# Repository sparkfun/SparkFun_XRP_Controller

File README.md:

SparkFun XRP Controller
========================================

<table>
    <tr>
        <td></td>
        <td></td>
    </tr>
    <tr>
        <th style="text-align: center;"><a href="https://www.sparkfun.com/sparkfun-experiential-robotics-platform-xrp-controller.html"><i>SparkFun XRP Controller</i></a></th>
        <th style="text-align: center;"><a href="https://www.sparkfun.com/sparkfun-experiential-robotics-platform-xrp-controller-beta.html"><i>SparkFun XRP Controller - Beta</i></a></th>
    </tr>
</table>

The Experiential Robotics Platform (XRP) Controller and Experiential Robotics Platform (XRP) Controller - Beta operate as the "brains" of the Experiential Robotics Platform Kits. These boards provide the programming and operation interface to connect and control the motors, sensors and other peripherals included in the XRP Kits. The controller boards primary microcontrollers are a Pico W (XRP-Beta) and RP2350 (XRP) and also include motor drivers, 6 DoF IMU, motor and sensor connectors along with other user interfaces.

Repository Contents
-------------------

* **/Documents** - Data sheets, additional product information
* **/Hardware** - Eagle design files (.brd, .sch)
* **/Production** - Production panel files (.brd)
* **/docs** - GitHub Pages documentation files (.md, images)

Documentation
--------------

* **[Hardware Overview](https://docs.sparkfun.com/SparkFun_XRP_Controller/introduction/)** - Basic hardware overview for the XRP Controller - Beta and XRP Controller.
* **[Experiential Robotics Platform Org](https://experientialrobotics.org/)** - Experiential Robotics Platform homepage.

Product Versions
----------------

* [ROB-22727](https://www.sparkfun.com/sparkfun-experiential-robotics-platform-xrp-controller-beta.html) - XRP Controller - Beta
* [ROB-26619](https://www.sparkfun.com/sparkfun-experiential-robotics-platform-xrp-controller.html) - XRP Controller

License Information
-------------------

This product is ***open source***!

Please review the LICENSE.md file for license information.

If you have any questions or concerns on licensing, please contact technical support on our [SparkFun forums](https://forum.sparkfun.com/viewforum.php?f=152).

Distributed as-is; no warranty is given.

* Your friends at SparkFun.

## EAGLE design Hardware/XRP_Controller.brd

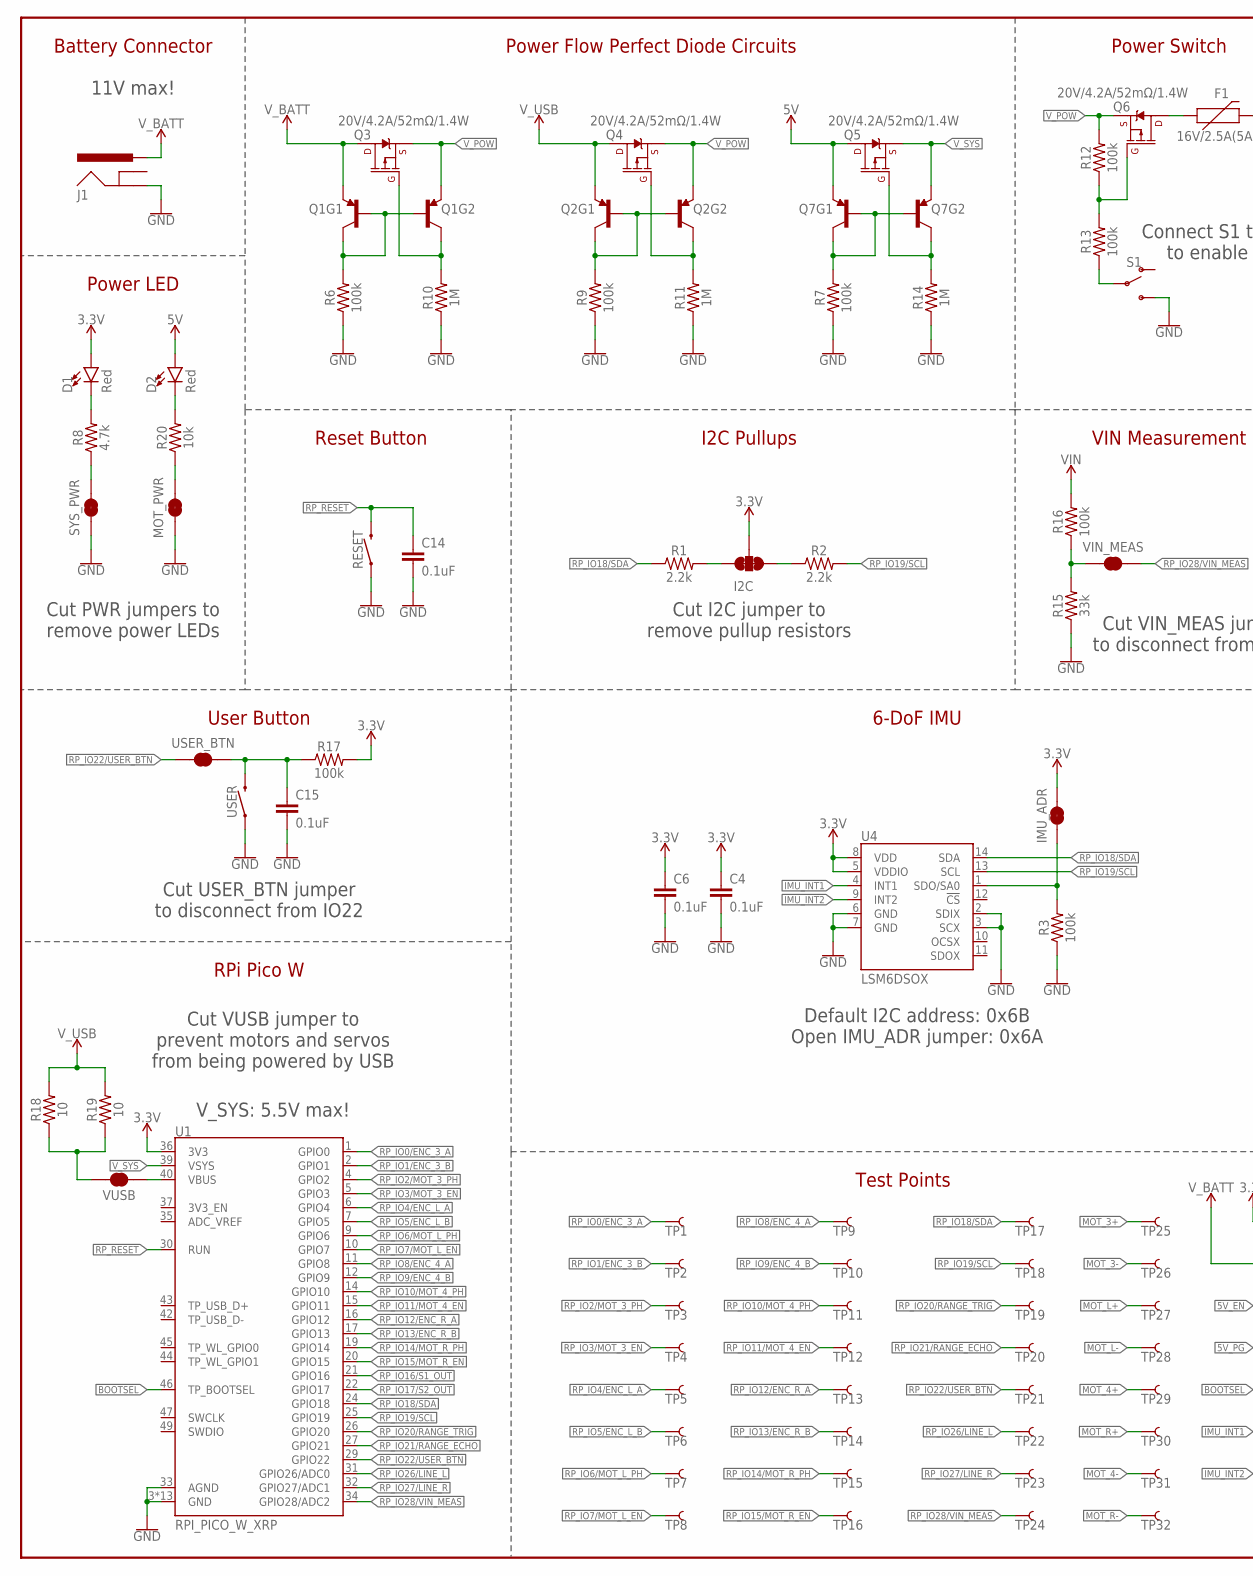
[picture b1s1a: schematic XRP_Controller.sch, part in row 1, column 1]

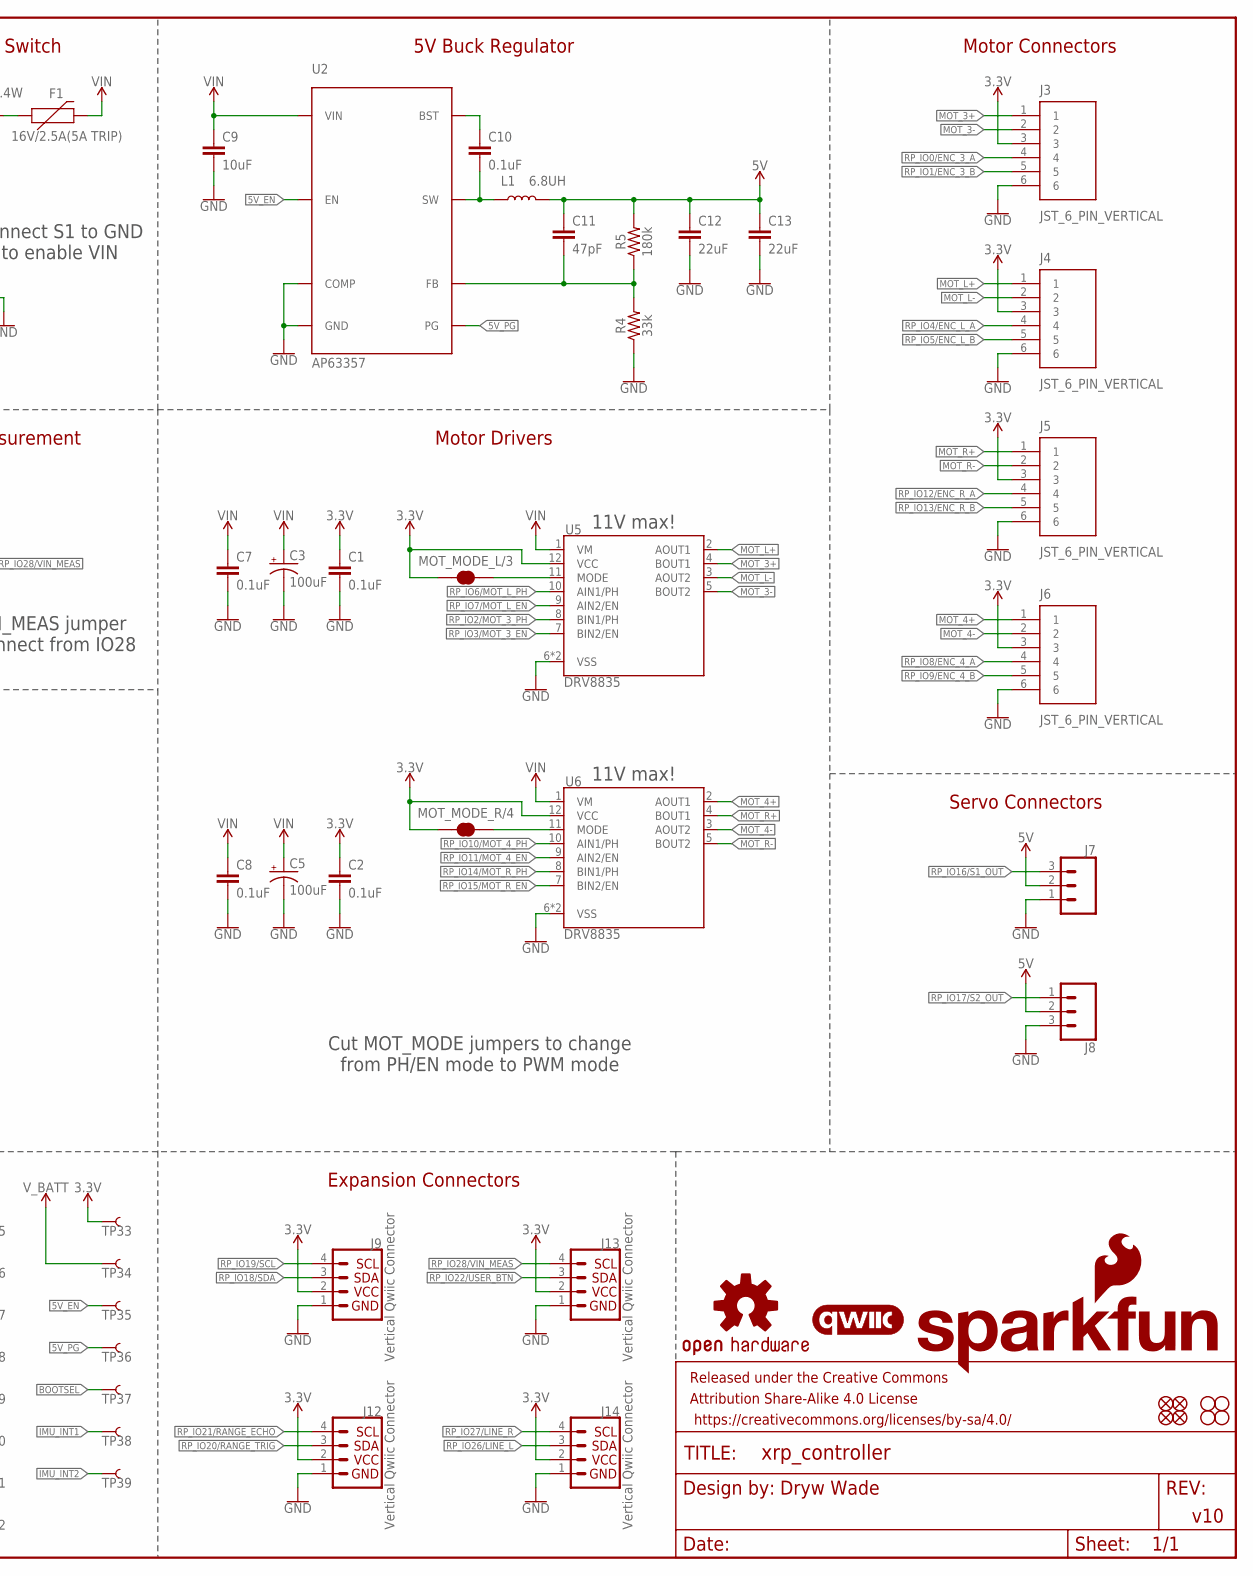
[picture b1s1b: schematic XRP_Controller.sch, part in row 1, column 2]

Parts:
C1, C2, C4, C6, C7, C8, C10, C14, C15: 0.1uF; 0603
C3, C5: 100uF; PANASONIC_D
C9: 10uF; 0805
C11: 47pF; 0603
C12, C13: 22uF; 0805
D1, D2: Red; LED-0603
F1: 16V/2.5A(5A TRIP); 1812
FD1, FD2, FD3, FD4: FIDUCIAL1X2; FIDUCIAL-1X2
FRAME1: FRAME-LEDGER; CREATIVE_COMMONS
H1, H2, H3, H4: STAND-OFF
I2C: JUMPER-SMT_3_2-NC_TRACE_SILK; SMT-JUMPER_3_2-NC_TRACE_SILK
IMU_ADR: JUMPER-SMT_2_NC_TRACE_SILK; SMT-JUMPER_2_NC_TRACE_SILK
J1: POWER_JACKPOWER_JACK_SLOT; POWER_JACK_PTH_SLOT
J3, J4, J5, J6: JST_6_PIN_VERTICAL; JST-6-SMD-VERT-1.0MM
J7, J8: CONN_03LOCK_NO_SILK; 1X03_LOCK_NO_SILK
J9, J12, J13, J14: Vertical Qwiic Connector; JST04_1MM_VERT
L1: 6.8UH; 07A7_6U8H
LOGO1: OSHW-LOGOS; OSHW-LOGO-S
LOGO3: SFE_LOGO_NAME_FLAME.3_INCH; SFE_LOGO_NAME_FLAME_.3
MOT_MODE_L/3: JUMPER-SMT_2_NC_TRACE_SILK; SMT-JUMPER_2_NC_TRACE_SILK
MOT_MODE_R/4: JUMPER-SMT_2_NC_TRACE_SILK; SMT-JUMPER_2_NC_TRACE_SILK
MOT_PWR: JUMPER-SMT_2_NC_TRACE_SILK; SMT-JUMPER_2_NC_TRACE_SILK
Q1, Q2, Q7: TRANS_PNP_DUALSOT-363; SOT363_PHILIPS
Q3, Q4, Q5, Q6: 20V/4.2A/52mΩ/1.4W; SOT23-3
R1, R2: 2.2k; 0603
R3, R6, R7, R9, R12, R13, R16, R17: 100k; 0603
R4, R15: 33k; 0603
R5: 180k; 0603
R8: 4.7k; 0603
R10, R11, R14: 1M; 0603
R18, R19: 10; 1206
R20: 10k; 0603
RESET: MOMENTARY-SWITCH-SPST-SMD-4.6X2.8MM; TACTILE_SWITCH_SMD_4.6X2.8MM
S1: SWITCH-SPDT-SMD-RIGHT-ANGLE; SWITCH_SPST_SMD_A
SYS_PWR: JUMPER-SMT_2_NC_TRACE_SILK; SMT-JUMPER_2_NC_TRACE_SILK
TP1, TP2, TP3, TP4, TP5, TP6, TP7, TP8, TP9, TP10, TP11, TP12, TP13, TP14, TP15, TP16, TP17, TP18, TP19, TP20, TP21, TP22, TP23, TP24, TP25, TP26, TP27, TP28, TP29, TP30, TP31, TP32, TP33, TP34, TP35, TP36, TP37, TP38, TP39: TEST-POINT3X5; PAD.03X.05
U1: RPI_PICO_W_XRP; RPI_PICO_W
U2: AP63357; V-DFN3020-13
U4: LSM6DSOX; LGA14L
U5, U6: DRV8835; WSON-12
U$98: QWIIC_LOGO_5MM_INVERTED; QWIIC_5MM_INVERTED
USER: MOMENTARY-SWITCH-SPST-SMD-4.6X2.8MM; TACTILE_SWITCH_SMD_4.6X2.8MM
USER_BTN: JUMPER-SMT_2_NC_TRACE_SILK; SMT-JUMPER_2_NC_TRACE_SILK
VIN_MEAS: JUMPER-SMT_2_NC_TRACE_SILK; SMT-JUMPER_2_NC_TRACE_SILK
VUSB: JUMPER-SMT_2_NC_TRACE_SILK; SMT-JUMPER_2_NC_TRACE_SILK

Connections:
3.3V: C1.1, C2.1, C4.1, C6.1, D1.A, I2C.2, IMU_ADR.2, J3.3, J4.3, J5.3, J6.3, J9.2, J12.2, J13.2, J14.2, MOT_MODE_L/3.2, MOT_MODE_R/4.2, R17.2, TP33.1, U1.36 (3V3), U4.5 (VDDIO), U4.8 (VDD), U5.12 (VCC), U6.12 (VCC)
5V: C11.1, C12.1, C13.1, D2.A, J7.2, J8.2, L1.P$2 (2), Q5.3 (D), Q7.1 (E), R5.2
5V_EN: TP35.1, U2.P$2 (EN)
5V_PG: TP36.1, U2.P$5 (PG)
!POW_EN!: R13.1, S1.2
!RP_RESET!: C14.1, RESET.3 (2), RESET.4 (2), U1.30 (RUN)
BOOTSEL: TP37.1, U1.46 (TP_BOOTSEL)
FB: C11.2, R4.2, R5.1, U2.P$3 (FB)
GND: C1.2, C2.2, C3.-, C4.2, C5.-, C6.2, C7.2, C8.2, C9.2, C12.2, C13.2, C14.2, C15.2, J1.GND, J3.6, J4.6, J5.6, J6.6, J7.1, J8.3, J9.1, J12.1, J13.1, J14.1, MOT_PWR.1, R3.1, R4.1, R6.1, R7.1, R9.1, R10.1, R11.1, R14.1, R15.1, RESET.1, RESET.2 (1), S1.3 (S), SYS_PWR.1, U1.3 (GND), U1.8 (GND), U1.13 (GND), U1.18 (GND), U1.23 (GND), U1.28 (GND), U1.33 (AGND), U1.38 (GND), U1.41 (GND), U1.48 (GND), U1.A (GND), U1.B (GND), U1.C (GND), U1.D (GND), U2.P$4 (COMP), U2.P$8 (GND), U4.2 (SDIX), U4.3 (SCX), U4.6 (GND), U4.7 (GND), U5.6 (VSS), U5.PAD (VSS), U6.6 (VSS), U6.PAD (VSS), USER.1, USER.2 (1)
IMU_INT1: TP38.1, U4.4 (INT1)
IMU_INT2: TP39.1, U4.9 (INT2)
MOT_3+: J3.1, TP25.1, U5.4 (BOUT1)
MOT_3-: J3.2, TP26.1, U5.5 (BOUT2)
MOT_4+: J6.1, TP29.1, U6.2 (AOUT1)
MOT_4-: J6.2, TP31.1, U6.3 (AOUT2)
MOT_L+: J4.1, TP27.1, U5.2 (AOUT1)
MOT_L-: J4.2, TP28.1, U5.3 (AOUT2)
MOT_R+: J5.1, TP30.1, U6.4 (BOUT1)
MOT_R-: J5.2, TP32.1, U6.5 (BOUT2)
unnamed: D1.C, R8.2
unnamed: IMU_ADR.1, R3.2, U4.1 (SDO/SA0)
unnamed: I2C.3, R1.2
unnamed: I2C.1, R2.1
unnamed: C10.1, U2.P$6 (BST)
unnamed: Q1.2 (B), Q1.5 (B), Q1.6 (C), R6.2
unnamed: Q1.3 (C), Q3.1 (G), R10.2
unnamed: F1.1, Q6.3 (D)
unnamed: U1.40 (VBUS), VUSB.2
unnamed: R8.1, SYS_PWR.2
unnamed: Q2.2 (B), Q2.5 (B), Q2.6 (C), R9.2
unnamed: R15.2, R16.1, VIN_MEAS.2
unnamed: MOT_MODE_L/3.1, U5.11 (MODE)
unnamed: MOT_MODE_R/4.1, U6.11 (MODE)
unnamed: Q6.1 (G), R12.1, R13.2
unnamed: Q2.3 (C), Q4.1 (G), R11.2
unnamed: C15.1, R17.1, USER.3 (2), USER.4 (2), USER_BTN.1
unnamed: R18.1, R19.1, VUSB.1
unnamed: Q7.2 (B), Q7.5 (B), Q7.6 (C), R7.2
unnamed: Q5.1 (G), Q7.3 (C), R14.2
unnamed: D2.C, R20.2
unnamed: MOT_PWR.2, R20.1
RP_IO0/ENC_3_A: J3.4, TP1.1, U1.1 (GPIO0)
RP_IO1/ENC_3_B: J3.5, TP2.1, U1.2 (GPIO1)
RP_IO2/MOT_3_PH: TP3.1, U1.4 (GPIO2), U5.8 (BIN1/PH)
RP_IO3/MOT_3_EN: TP4.1, U1.5 (GPIO3), U5.7 (BIN2/EN)
RP_IO4/ENC_L_A: J4.4, TP5.1, U1.6 (GPIO4)
RP_IO5/ENC_L_B: J4.5, TP6.1, U1.7 (GPIO5)
RP_IO6/MOT_L_PH: TP7.1, U1.9 (GPIO6), U5.10 (AIN1/PH)
RP_IO7/MOT_L_EN: TP8.1, U1.10 (GPIO7), U5.9 (AIN2/EN)
RP_IO8/ENC_4_A: J6.4, TP9.1, U1.11 (GPIO8)
RP_IO9/ENC_4_B: J6.5, TP10.1, U1.12 (GPIO9)
RP_IO10/MOT_4_PH: TP11.1, U1.14 (GPIO10), U6.10 (AIN1/PH)
RP_IO11/MOT_4_EN: TP12.1, U1.15 (GPIO11), U6.9 (AIN2/EN)
RP_IO12/ENC_R_A: J5.4, TP13.1, U1.16 (GPIO12)
RP_IO13/ENC_R_B: J5.5, TP14.1, U1.17 (GPIO13)
RP_IO14/MOT_R_PH: TP15.1, U1.19 (GPIO14), U6.8 (BIN1/PH)
RP_IO15/MOT_R_EN: TP16.1, U1.20 (GPIO15), U6.7 (BIN2/EN)
RP_IO16/S1_OUT: J7.3, U1.21 (GPIO16)
RP_IO17/S2_OUT: J8.1, U1.22 (GPIO17)
RP_IO18/SDA: J9.3, R1.1, TP17.1, U1.24 (GPIO18), U4.14 (SDA)
RP_IO19/SCL: J9.4, R2.2, TP18.1, U1.25 (GPIO19), U4.13 (SCL)
RP_IO20/RANGE_TRIG: J12.3, TP19.1, U1.26 (GPIO20)
RP_IO21/RANGE_ECHO: J12.4, TP20.1, U1.27 (GPIO21)
RP_IO22/USER_BTN: J13.3, TP21.1, U1.29 (GPIO22), USER_BTN.2
RP_IO26/LINE_L: J14.3, TP22.1, U1.31 (GPIO26/ADC0)
RP_IO27/LINE_R: J14.4, TP23.1, U1.32 (GPIO27/ADC1)
RP_IO28/VIN_MEAS: J13.4, TP24.1, U1.34 (GPIO28/ADC2), VIN_MEAS.1
SW: C10.2, L1.P$1 (1), U2.P$7 (SW), U2.P$9 (SW)
VIN: C3.+, C5.+, C7.1, C8.1, C9.1, F1.2, R16.2, U2.P$1 (VIN), U5.1 (VM), U6.1 (VM)
V_BATT: J1.PWR, Q1.1 (E), Q3.3 (D), TP34.1
V_POW: Q1.4 (E), Q2.4 (E), Q3.2 (S), Q4.2 (S), Q6.2 (S), R12.2
V_SYS: Q5.2 (S), Q7.4 (E), U1.39 (VSYS)
V_USB: Q2.1 (E), Q4.3 (D), R18.2, R19.2

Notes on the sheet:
Dryw Wade
v10
Motor Connectors
Servo Connectors
Expansion Connectors
Battery Connector
Motor Drivers
RPi Pico W
6-DoF IMU
Power LED
Reset Button
11V max!
5V Buck Regulator
Power Flow Perfect Diode Circuits
Power Switch
I2C Pullups
Cut I2C jumper to remove pullup resistors
Default I2C address: 0x6B Open IMU_ADR jumper: 0x6A
Cut PWR jumpers to remove power LEDs
Cut VUSB jumper to prevent motors and servos from being powered by USB
Cut MOT_MODE jumpers to change from PH/EN mode to PWM mode
Connect S1 to GND to enable VIN
Test Points
VIN Measurement
Cut VIN_MEAS jumper to disconnect from IO28
User Button
Cut USER_BTN jumper to disconnect from IO22
V_SYS: 5.5V max!

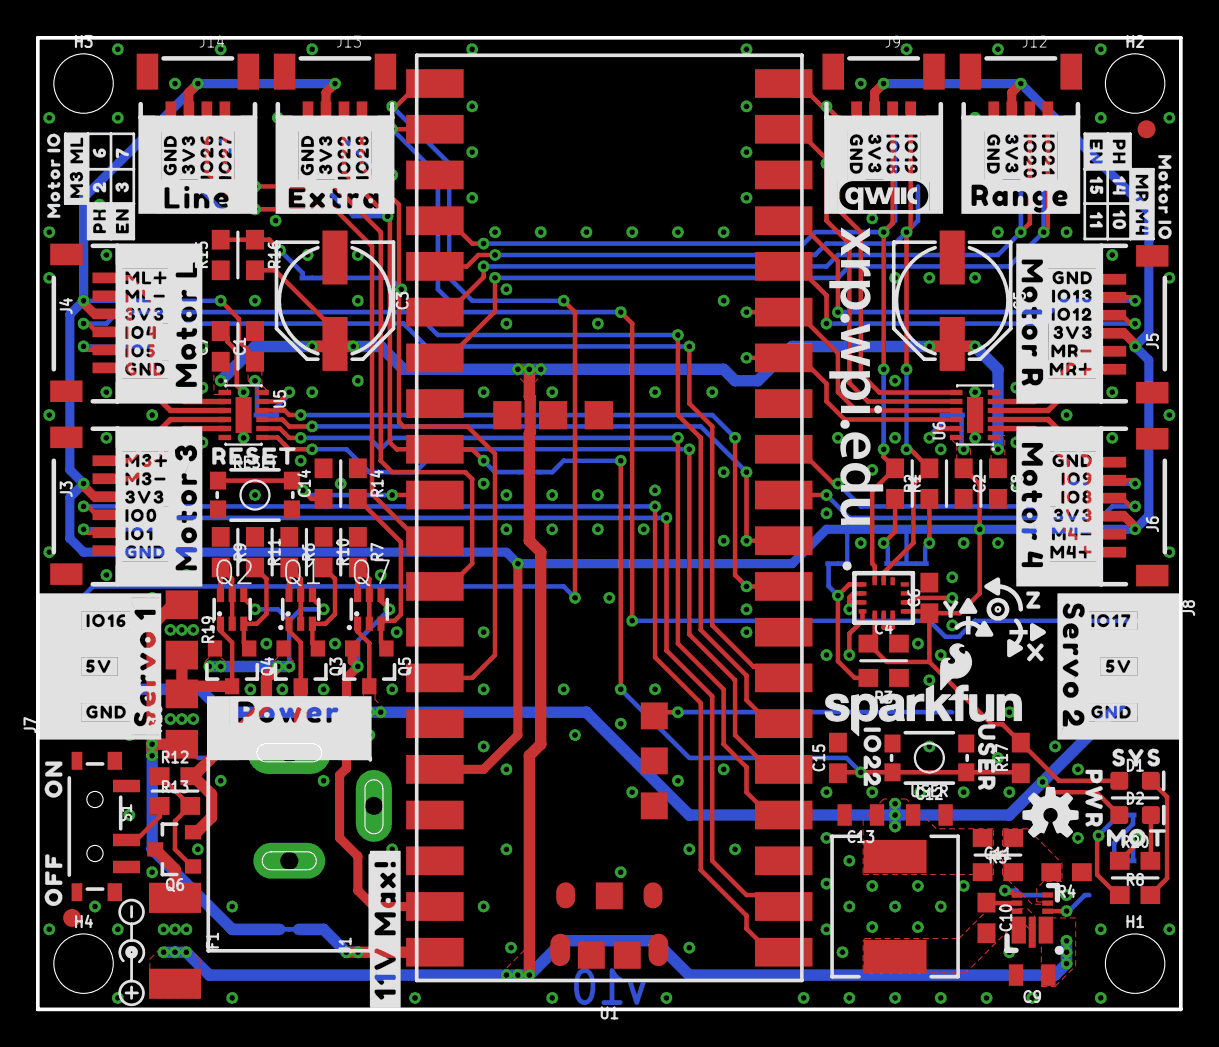
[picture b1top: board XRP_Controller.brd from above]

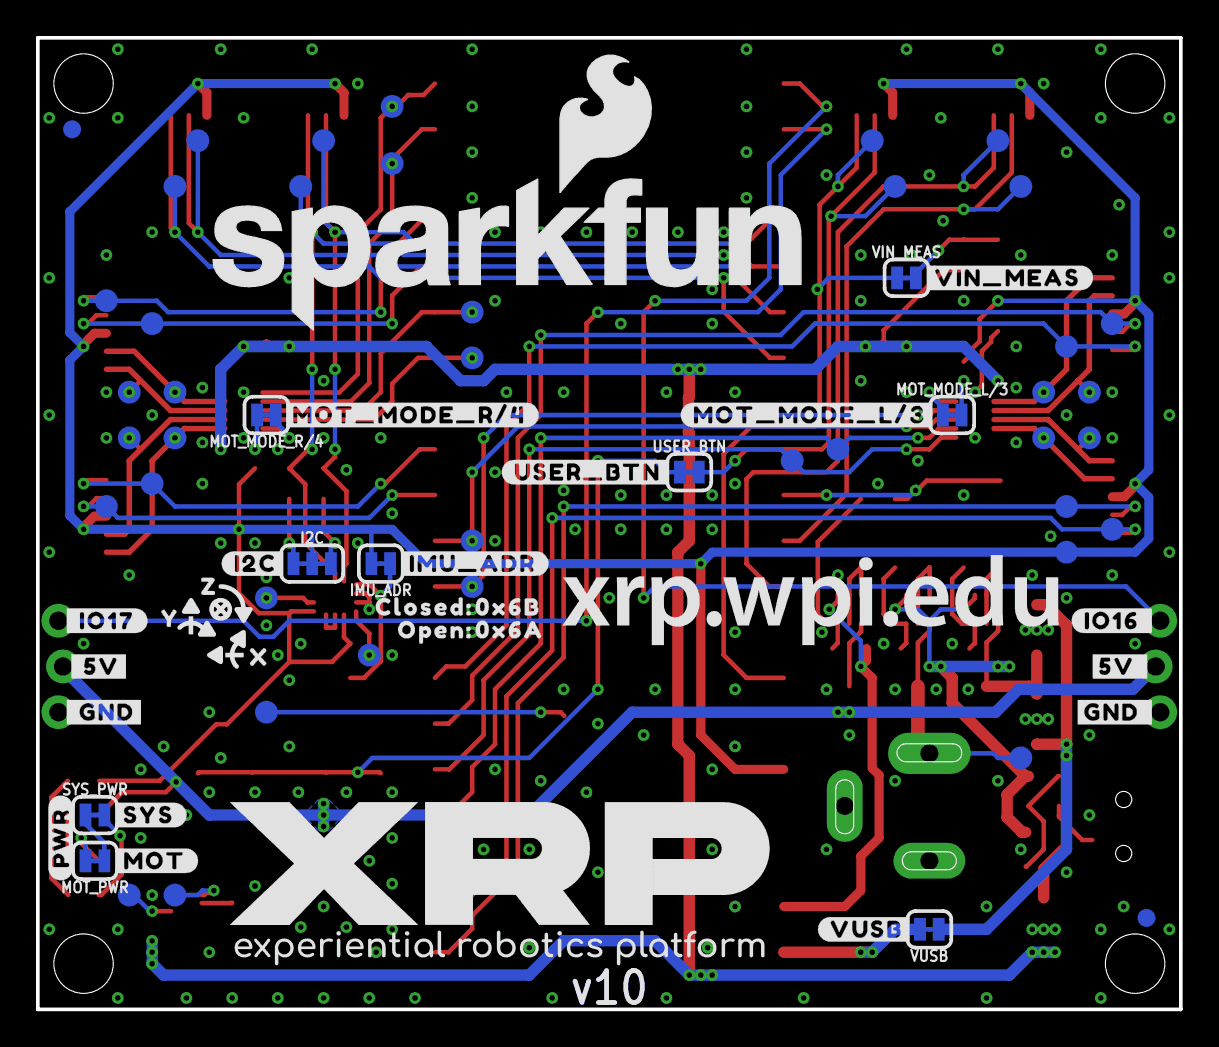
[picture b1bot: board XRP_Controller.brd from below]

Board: 2 copper layers, 63.5 x 54.0 mm, 240 parts (76 on the bottom side), 73 nets.

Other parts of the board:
LOGO4: SFE_LOGO_NAME_FLAME.1_INCH; SFE_LOGO_NAME_FLAME_.1
U$1: #MOTOR_3#0
U$2: #SERVO_2#0
U$3: #11V_MAX###0
U$4, U$24, U$50, U$52, U$54: #GND#0
U$5: #POWER#0
U$6: PWR0
U$7: RESET0
U$8: #MOTOR_R#0
U$9: #MR##0
U$10: #MOTOR_L#0
U$11: #SERVO_1#0
U$12: #MOTOR_4#0
U$13: #VIN_MEAS#0
U$14: #MR##1
U$15, U$25, U$51, U$53: #3V3#0
U$16: #ML##0
U$17, U$33, U$41, U$43: #3V3#4
U$18: #M4##0
U$19: #M4##5
U$20: #IO0#0
U$21: #IO1#0
U$22: #IO5#0
U$23: #IO4#0
U$26: #GND_#0
U$27: #5V_#0
U$28: #IO8#0
U$29: #IO9#0
U$30, U$31, U$40, U$42, U$57: #GND#10
U$32: #ML##1
U$34: #IO12#0
U$35: #IO13#0
U$36: ORDERING_INSTRUCTIONS
U$37, U$117: #PH#0
U$38: #IO27#0
U$39: #IO28#0
U$44: #IO26#0
U$45: #IO22#0
U$46: #IO18#0
U$47: #IO19#0
U$48: #IO20#0
U$49: #IO21#0
U$55: #5V#0
U$56: #IO16#0
U$58: #IO17#0
U$59: #5V#18
U$60: #I2C#0
U$61: #IO16_#0
U$62: ON0
U$63: OFF0
U$64: #IMU_ADR#0
U$65, U$116: #EN#0
U$66: #MOT_MODE_L#3#0
U$67: SYS0
U$68: IO220
U$69: #RANGE#0
U$70: #MOT_MODE_R#4#0
U$71: MOT0
U$72: XRP_URL_3MM
U$73: #PWR#0
U$74: #LINE#0
U$75: #_GND#0
U$76: #_5V#0
U$77: #_IO17#0
U$78: POLARITY_MARKING_CENTER_POSITIVE#JPG
U$79, U$88: X0
U$80, U$89: Y0
U$81, U$90: Z0
U$82: #EXTRA#0
U$83: USER0
U$84: #USER_BTN#0
U$85: 0X6B0
U$86: 0X6A0
U$87: OPEN#0
U$91: CLOSED#0
U$92: XRP_FULL_LOGO
U$93: #VUSB#0
U$94: #M3##0
U$95: #MOT#0
U$96: #SYS#0
U$97: XRP_URL_5MM
U$99: #M3##4
U$100: #ML#0
U$101: #M3#0
U$102: 100
U$103: 110
U$104: 140
U$105: 150
U$106: #MR#0
U$107: #M4#0
U$108: 20
U$109: 30
U$110: 60
U$111: 70
U$114, U$115: MOTOR_IO0

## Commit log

2023-01-18 Create Pico W library file
2023-01-18 Add initial schematic and board layout
2023-01-18 Add datasheets
2023-01-18 Clean up schematic
    Add dashed lines between regions
    Add I2C address for IMU
    Add max voltages for motor drivers, 5V regulator, and Pico W
    Rename jumpers and indicate functions
2023-01-19 Design review updates
    Replace 2 power switch FETs with 1 at output of perfect diodes
    Add perfect diode to make Pico's VSYS be input only
    Extend board length to 2.125in
    Move reset button away from edge, to center of left side
    Swap right side motor IO pins
    Rename connectors and corresponding nets
2023-01-19 Design review updates
    Add debounce capacitor to reset button
    Increase power trace widths to 25 mils
    Pull 5V polygon out from under inductor and add GND vias
2023-01-19 Design review updates
    Add silk lines between adjacent passive components
    Rename "!EN!" net to "!POW_EN!"
    Add text next to power switch indicating function
2023-01-20 Design review updates
    Pico footprint:
    Change pad and paste geometry based on DFM feedback (no copper or paste under the inner holes of the Pico's pads), and over paste outside of pads for better fillets)
    Reduce paste under test points
    Remove paste from USB PTH pads
    Schematic:
    Nudge power MOSFET to prevent !POW_EN! flag from overlapping net
2023-01-25 Add proto production files
2023-01-30 v02 updates
    Bump version number
    Add tKeepout, tName and tValue to Pico W footprint
    Reorganize schematic
    Change servo header to locking footprint
    Add test points for all GPIO pins
    Add inverted Qwiic logo
2023-02-13 Update Pico W footprint tDocu
    Now with more accurate pad geometry!
2023-02-13 Update buck footprint with reduced paste
2023-02-13 Nudge servo silk to improve readability
2023-03-01 Design review updates
    Move version number in schematic to correct location
    Rename 2nd expansion connector from "Range" to "Extra"
    Rename 4th expansion connector from "Conn4" to "Range"
    Add VIN measurement through voltage divider and NC jumper to IO28
    Add V_BATT test point
2023-03-06 Design review updates
    Schematic:
    Restore Q6 value
    Add user button to IO22 via NC jumper
    Move USB_POW next to Pico W
    Add current limiting resistor to VUSB
    Board:
2023-03-15 v10 updates
    Bump version number to v10
    Update Pico W datasheet
    Change Pico W footprint to match datasheet recommendations
    Nudge inner expansion connectors inwards to be on 0.05" grid
    Rename USB_POW jumper to VUSB
    Replace PWR_LED jumper silk label with PWR
2023-03-15 Minor routing improvments
    Nudge a couple traces to improve GND continuity
2023-03-17 Update VUSB path
    Replace R18 with 2x 1206 10 Ohm resistors in parallel (better power rating than a single 0603)
    Change VUSB jumper from NO to NC
    Flip 3V3 and VBUS pins of Pico W footprint
2023-03-17 Design review updates
    Add IO22 silk label to user button
    Move VUSB jumper under V_SYS label in schematic
    Renumber last few test points
    Add test point for IMU interrupt pin
2023-03-17 Minor tweaks
    Nudge C3 to be on grid
    Move MOT_3_EN via to not overlap with RESET silk
    Nudge V_SYS trace and reduce width to get better GND pour
2023-03-17 Fix "Range" silk
    Modify the Buzzard footprint to have a lower bottom edge
2023-03-20 Connect SCX pin of IMU to GND
    Datasheet says to do this, whoops!
    Pins 10-12 have internal pullups, can leave unconnected
2023-03-20 Put all XRP specific parts into a single library
    Helps ensure PROD_ID values are correct for this project
2023-03-20 Update RP2040 and IMU datasheets
2023-03-21 Nudge vias to clean up silk text
2023-03-21 Minor tweaks
    Nudge I2C jumper back onto grid
    Nudge a couple power traces under Pico W
2023-03-22 Design review updates
    Motor mode jumpers - add "/3" and "/4" to jumper names
    Overlay copper version number with silk version number
    Change IMU_ADR jumper from NO to NC, and swap with R3 to keep same default address
    Add second power LED to indicate motor power vs system power
    Change power LEDs to DIO-17976 and corresponding resistor values
2023-03-23 Put OSHW logo back onto board
2023-03-31 Add OpenSTEM logos
2023-03-31 Add inverted Qwiic logo as library part
2023-03-31 v09 tweaks
    Ordering a few boards early before logos are finalized
    Removed URLs for now
2023-03-31 Add v09 panel files
2023-04-07 v10 updates
    Bump version number to v10
    Remove OpenSTEM logo
    Add XRP URL to top and bottom silk
    Nudge expansion connectors in schematic to not have overlapping labels
    Nudge Qwiic logo to get thicker silk along bottom edge
    Approve DRC overlap errors
2023-04-14 Minor tweaks
    Update buck footprint to link to SFE Eagle library
    Change motor nets and silk labels to use +/- instead of P/N
2023-04-14 Add ordering instructions
2023-04-14 Add v10 panel files
2023-04-25 Move user button
    Corner was not accessible enough in chassis. User button now takes the location of the XRP logo just under the SparkFun logo
2023-04-25 Fix GND flow
2023-04-25 Add motor IO silk to top corners
    Also remove extra via under user button
2023-04-27 Add silk lines between power LEDs and resistors
2023-04-27 Update v10 panel files
2023-06-15 Update Pico W with more paste on castellated pads
    Turns out the Pico W boards are slightly warped (about 100um), meaning pads at the ends are frequently not connected. More paste should help!
2023-06-22 Initial Docs Commit
    Initial docs commit. Adds Hardware Overview, photos & resources page along with necessary files for building GH Pages site.
2023-06-23 Update hardware overview
    Updating hardware overview doc for initial page publication.
2023-06-23 Editing fix
    Fixing SF logo & Experimental/Experiential typo
2023-06-27 Updating Buttons desc
    Updating buttons description to include BOOTSEL button. New photo highlighting BOOTSEL button.
2023-07-07 Update hardware_overview.md
    Updating hardware overview doc with minor fixes.
2023-09-07 Moved components to SFE Eagle libraries
2023-09-25 Update hardware_overview.md
    Small update to pinout table for missing GPIO pins
2023-10-26 Docs Update
    Adding single page files.
2023-10-26 Deployed 5270f1b with MkDocs version: 1.5.3
2024-10-25 Update mkdocs.yml
    Analytics update
2024-10-25 Deployed 383b9b1 with MkDocs version: 1.6.1
2025-02-25 Update product names & yml files
    Updating Hardware Overview & Resources documents with current XRP Beta product names. Updating main and workflows .yml files to current version.
2025-02-25 Deployed abaea07 with MkDocs version: 1.6.1
2025-03-13 XRP Release Update
    Creating merge branch for review before merging with main. This includes all files for updated documentation and adding hardware/production files for XRP "non-beta". File and folder movement and crea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
2025-03-13 Re-organize hardware files
2025-03-13 Re-organize production files
2025-03-13 Fix ordering instructions and add .drl file
2025-03-14 Deployed 003a7f0 with MkDocs version: 1.6.1
2025-03-14 Update introduction.md
    Fixing table rendering typos.
2025-03-14 Deployed e009b40 with MkDocs version: 1.6.1
2025-03-14 Minor docs edits
    Fixing image preview error on Introduction page & other small typos.
2025-03-14 Deployed 861792e with MkDocs version: 1.6.1
2025-03-17 Update XRP KiCad ZIP
    Updating XRP Controller KiCad ZIP folder with the correct files.
2025-03-17 Deployed 0f61d38 with MkDocs version: 1.6.1
2025-03-20 Update resources.md
    added new 3D printing files - Sean
2025-03-20 Deployed 18fdf86 with MkDocs version: 1.6.1
2025-03-25 Deployed 1271459 with MkDocs version: 1.6.1
2025-04-15 Resources Update
    Fixing hardware files & resources links .
2025-04-15 Deployed c84675a with MkDocs version: 1.6.1
2026-06-03 Deployed ce66d8b with MkDocs version: 1.6.1
2026-06-08 Update hardware_overview.md
    Updating barrel jack voltage range to clarify use of alternate battery types.
2026-06-08 Deployed 86c4cd7 with MkDocs version: 1.6.1

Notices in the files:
parts and their libraries:
SparkFun-Aesthetics: Licensing: Creative Commons ShareAlike 4.0 International - https://creativecommons.org/licenses/by-sa/4.0
SparkFun-Aesthetics: Released under the Creative Commons Attribution Share-Alike 4.0 License
SparkFun-Aesthetics: https://creativecommons.org/licenses/by-sa/4.0
